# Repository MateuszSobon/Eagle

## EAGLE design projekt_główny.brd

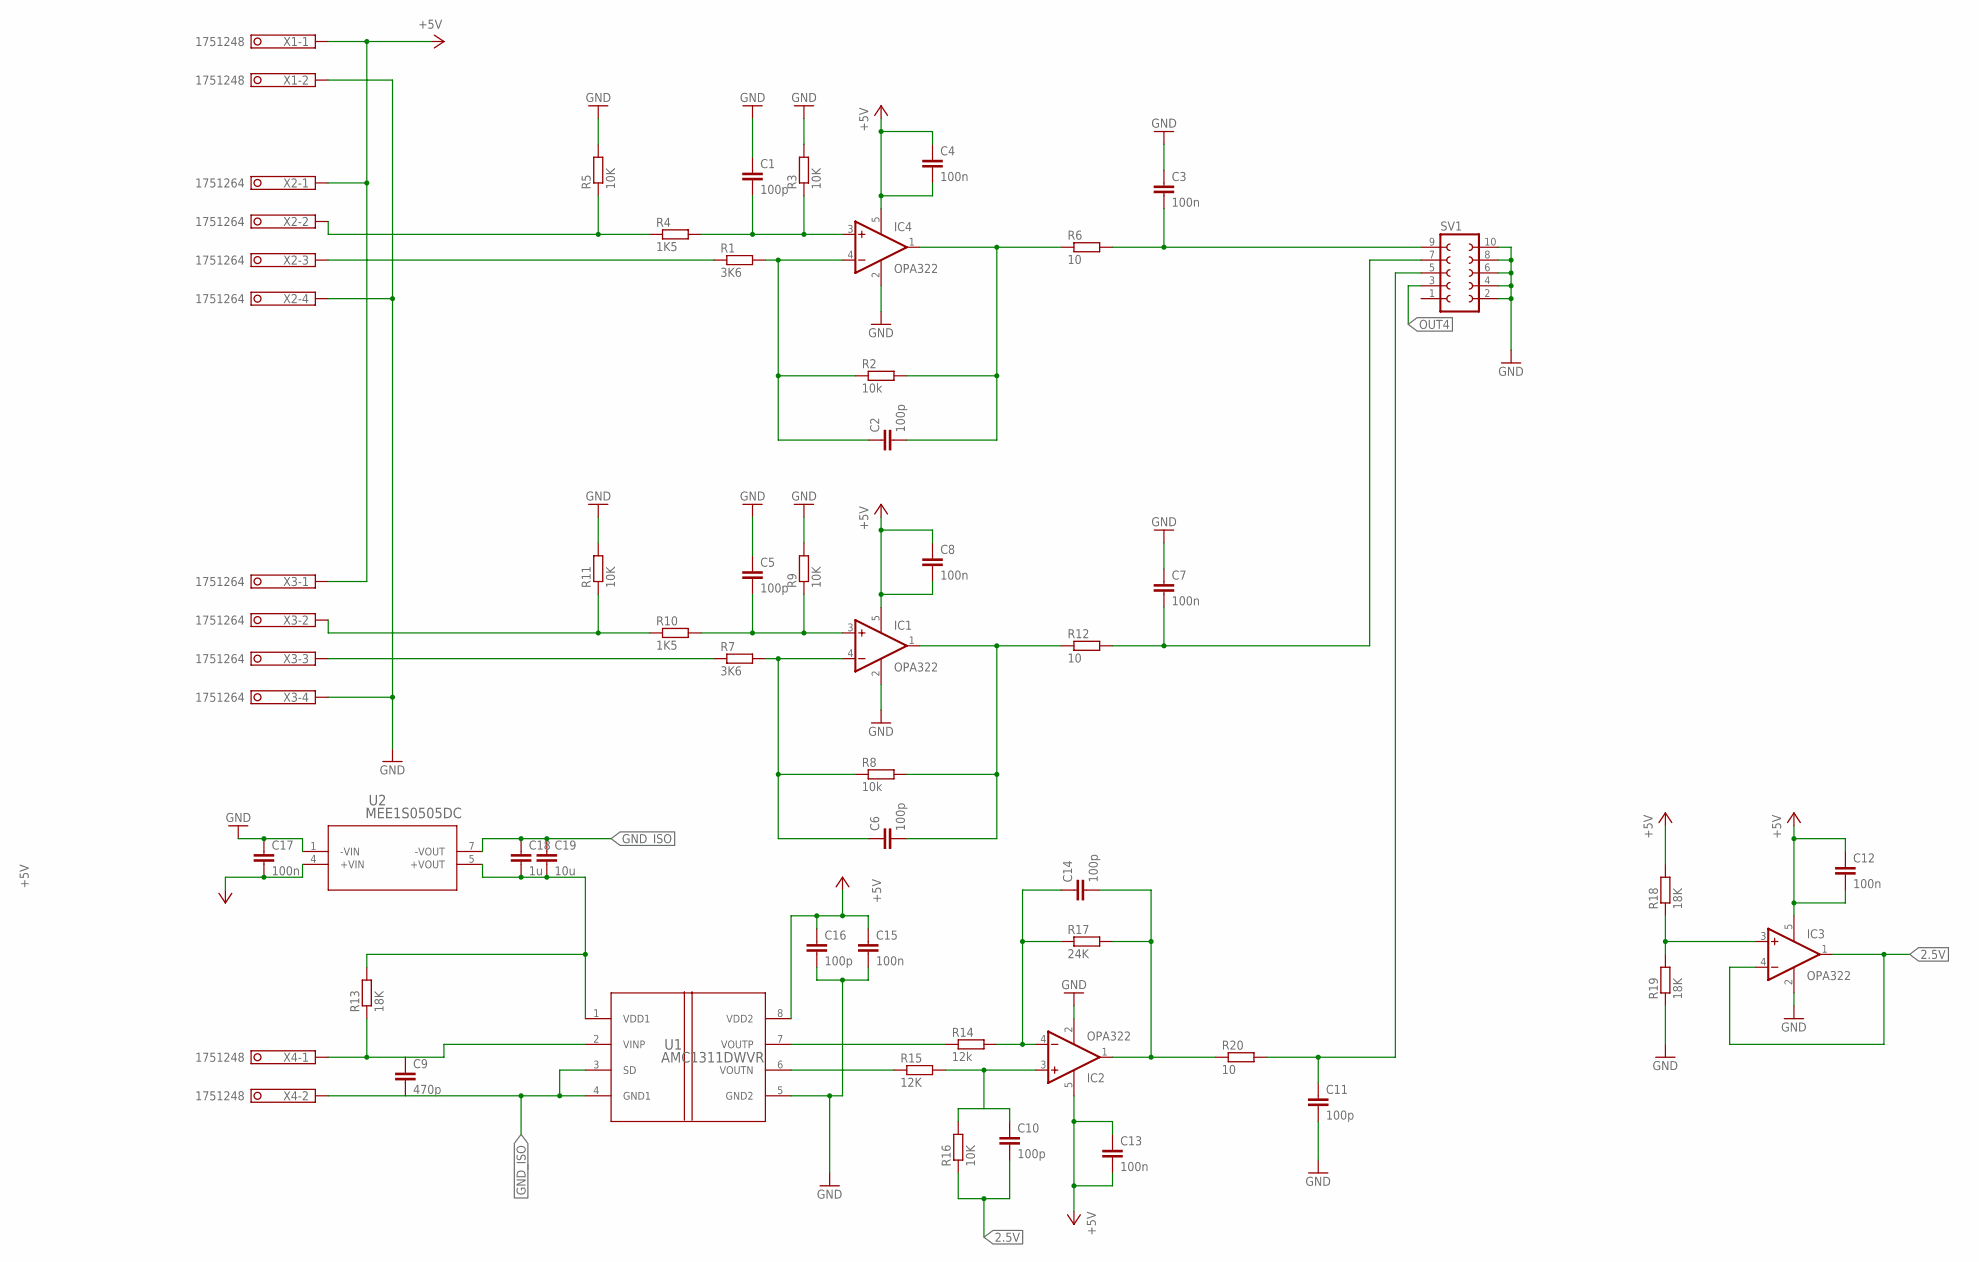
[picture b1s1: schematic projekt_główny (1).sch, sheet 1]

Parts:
C1, C2, C5, C6, C10, C11, C14, C16: 100p; C0603
C3, C4, C7, C8, C12, C13, C15, C17: 100n; C0603
C9: 470p; C0603
C18: 1u; C0603
C19: 10u; C0603
IC1, IC2, IC3, IC4: OPA322; SOT23-5
R1, R7: 3K6; R0805
R2, R8: 10k; R0805
R3, R5, R9, R11, R16: 10K; R0805
R4, R10: 1K5; R0805
R6, R12, R20: 10; R0805
R13, R18, R19: 18K; R0805
R14: 12k; R0805
R15: 12K; R0805
R17: 24K; R0805
SV1: FE05-2
U1: AMC1311DWVR; DWV0008A
U2: MEE1S0505DC; MEE1S0305DC_MUR
X1, X4: 1751248
X2, X3: 1751264

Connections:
2.5V: C10.2, IC3.1 (OUT), IC3.4 (-IN), R16.1; also elsewhere on the board
+5V: C4.1, C4.2, C8.1, C8.2, C12.1, C12.2, C13.1, C13.2, C15.1, C16.1, C17.2, IC1.5 (V+), IC2.5 (V+), IC3.5 (V+), IC4.5 (V+), R18.2, U1.8 (VDD2), U2.4 (+VIN), X1.1, X2.1, X3.1; also elsewhere on the board
GND: C1.1, C3.1, C5.1, C7.1, C11.2, C15.2, C16.2, C17.1, IC1.2 (V-), IC2.2 (V-), IC3.2 (V-), IC4.2 (V-), R3.2, R5.2, R9.2, R11.2, R19.1, SV1.2, SV1.4, SV1.6, SV1.8, SV1.10, U1.5 (GND2), U2.1 (-VIN), X1.2, X2.4, X3.4; also elsewhere on the board
GND_ISO: C9.2, C18.1, C19.1, U1.3 (SD), U1.4 (GND1), U2.7 (-VOUT), X4.2
unnamed: C2.1, IC4.4 (-IN), R1.2, R2.1
unnamed: R1.1, X2.3
unnamed: C2.2, IC4.1 (OUT), R2.2, R6.1
unnamed: C1.2, IC4.3 (+IN), R3.1, R4.2
unnamed: R4.1, R5.1, X2.2
unnamed: C3.2, R6.2, SV1.9
unnamed: C6.1, IC1.4 (-IN), R7.2, R8.1
unnamed: R7.1, X3.3
unnamed: C6.2, IC1.1 (OUT), R8.2, R12.1
unnamed: C5.2, IC1.3 (+IN), R9.1, R10.2
unnamed: R10.1, R11.1, X3.2
unnamed: C7.2, R12.2, SV1.7
unnamed: C9.1, R13.1, U1.2 (VINP), X4.1
unnamed: C14.1, IC2.4 (-IN), R14.2, R17.1
unnamed: IC3.3 (+IN), R18.1, R19.2
unnamed: R15.1, U1.6 (VOUTN)
unnamed: R14.1, U1.7 (VOUTP)
unnamed: C11.1, R20.2, SV1.5
unnamed: C14.2, IC2.1 (OUT), R17.2, R20.1
unnamed: C10.1, IC2.3 (+IN), R15.2, R16.2
unnamed: C18.2, C19.2, R13.2, U1.1 (VDD1), U2.5 (+VOUT)
OUT4: SV1.3; also elsewhere on the board

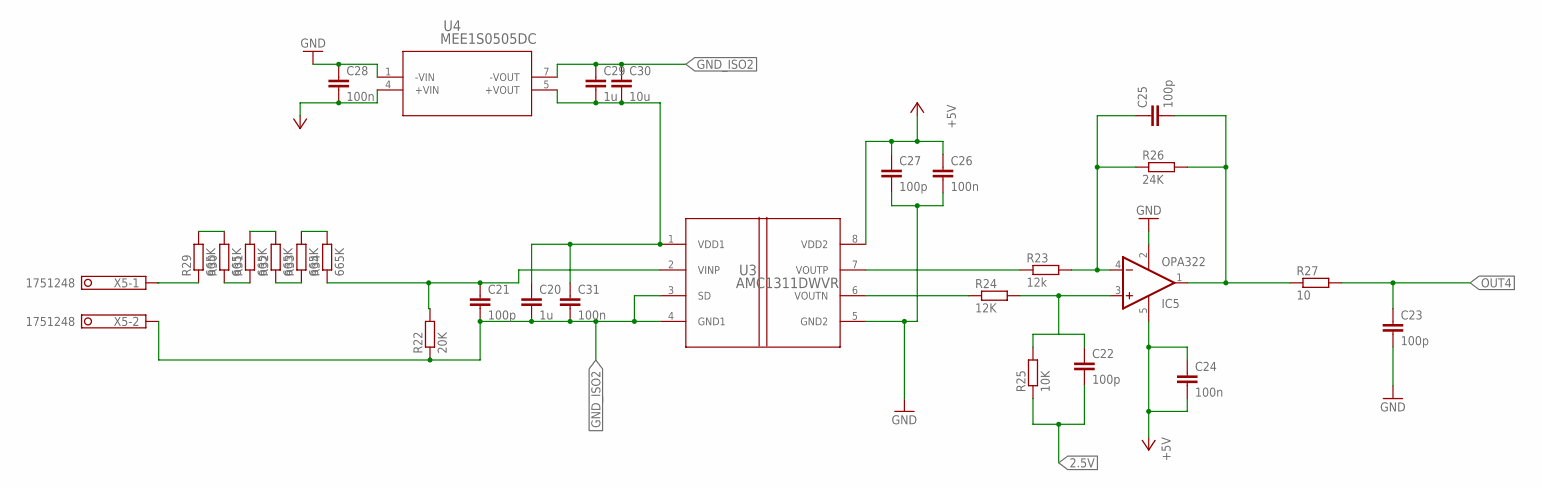
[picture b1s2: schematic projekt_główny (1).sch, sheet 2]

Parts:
C20, C29: 1u; C0603
C21, C22, C23, C25, C27: 100p; C0603
C24, C26, C28, C31: 100n; C0603
C30: 10u; C0603
IC5: OPA322; SOT23-5
R22: 20K; R0805
R23: 12k; R0805
R24: 12K; R0805
R25: 10K; R0805
R26: 24K; R0805
R27: 10; R0805
R29, R30, R31, R32, R33, R34: 665K; R0805
U3: AMC1311DWVR; DWV0008A
U4: MEE1S0505DC; MEE1S0305DC_MUR
X5: 1751248

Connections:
2.5V: C22.2, R25.1; also elsewhere on the board
+5V: C24.1, C24.2, C26.1, C27.1, C28.2, IC5.5 (V+), U3.8 (VDD2), U4.4 (+VIN); also elsewhere on the board
GND: C23.2, C26.2, C27.2, C28.1, IC5.2 (V-), U3.5 (GND2), U4.1 (-VIN); also elsewhere on the board
GND_ISO2: C20.2, C21.2, C29.1, C30.1, C31.2, R22.1, U3.3 (SD), U3.4 (GND1), U4.7 (-VOUT), X5.2
unnamed: C21.1, R22.2, R34.1, U3.2 (VINP)
unnamed: C25.1, IC5.4 (-IN), R23.2, R26.1
unnamed: R24.1, U3.6 (VOUTN)
unnamed: R23.1, U3.7 (VOUTP)
unnamed: C25.2, IC5.1 (OUT), R26.2, R27.1
unnamed: C22.1, IC5.3 (+IN), R24.2, R25.2
unnamed: C20.1, C29.2, C30.2, C31.1, U3.1 (VDD1), U4.5 (+VOUT)
unnamed: R33.2, R34.2
unnamed: R32.1, R33.1
unnamed: R31.2, R32.2
unnamed: R30.1, R31.1
unnamed: R29.2, R30.2
unnamed: R29.1, X5.1
OUT4: C23.1, R27.2; also elsewhere on the board

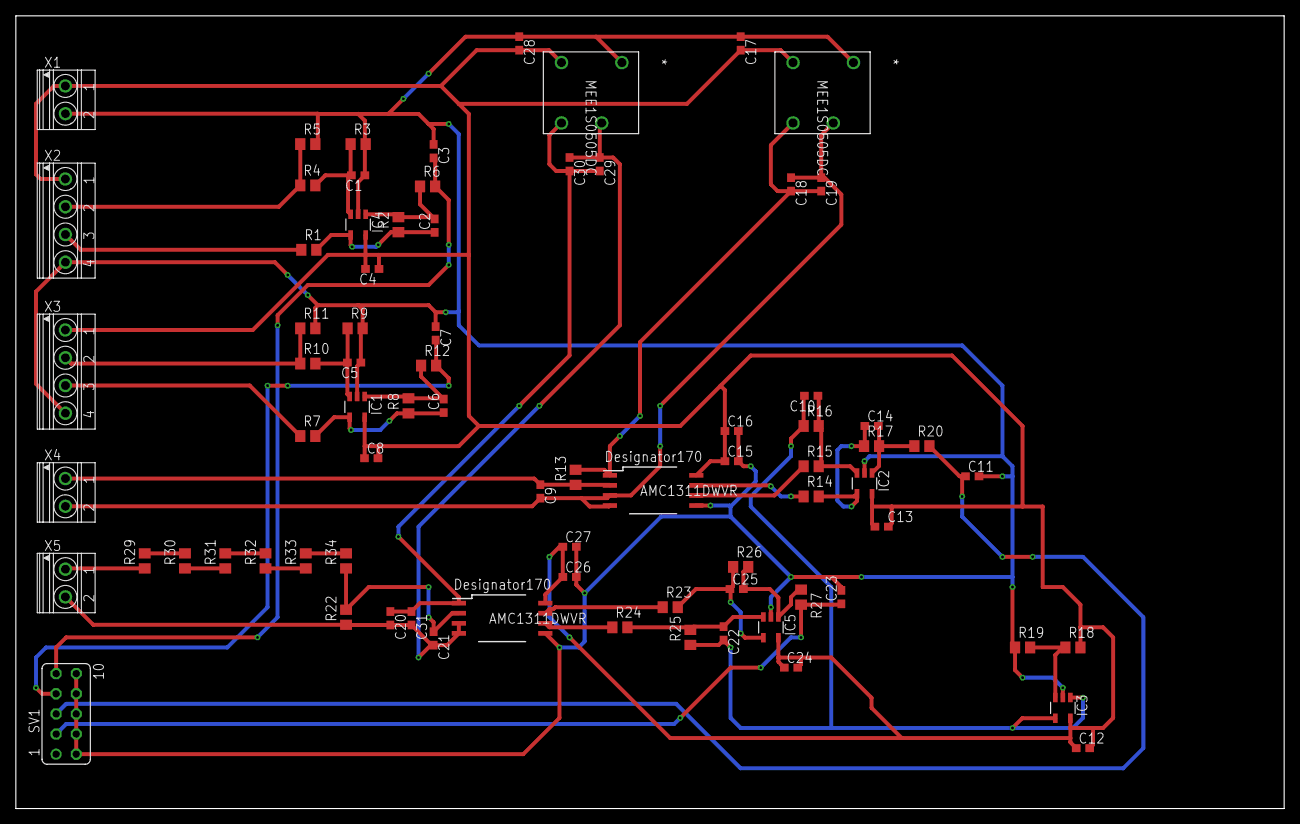
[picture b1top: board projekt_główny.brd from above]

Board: 2 copper layers, 160.0 x 100.0 mm, 78 parts (0 on the bottom side), 40 nets.

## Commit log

2023-04-18 Projekt PCB

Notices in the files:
parts and their libraries:
untitled: COPYRIGHT: Copyright (C) 2023 Ultra Librarian. All rights reserved.
